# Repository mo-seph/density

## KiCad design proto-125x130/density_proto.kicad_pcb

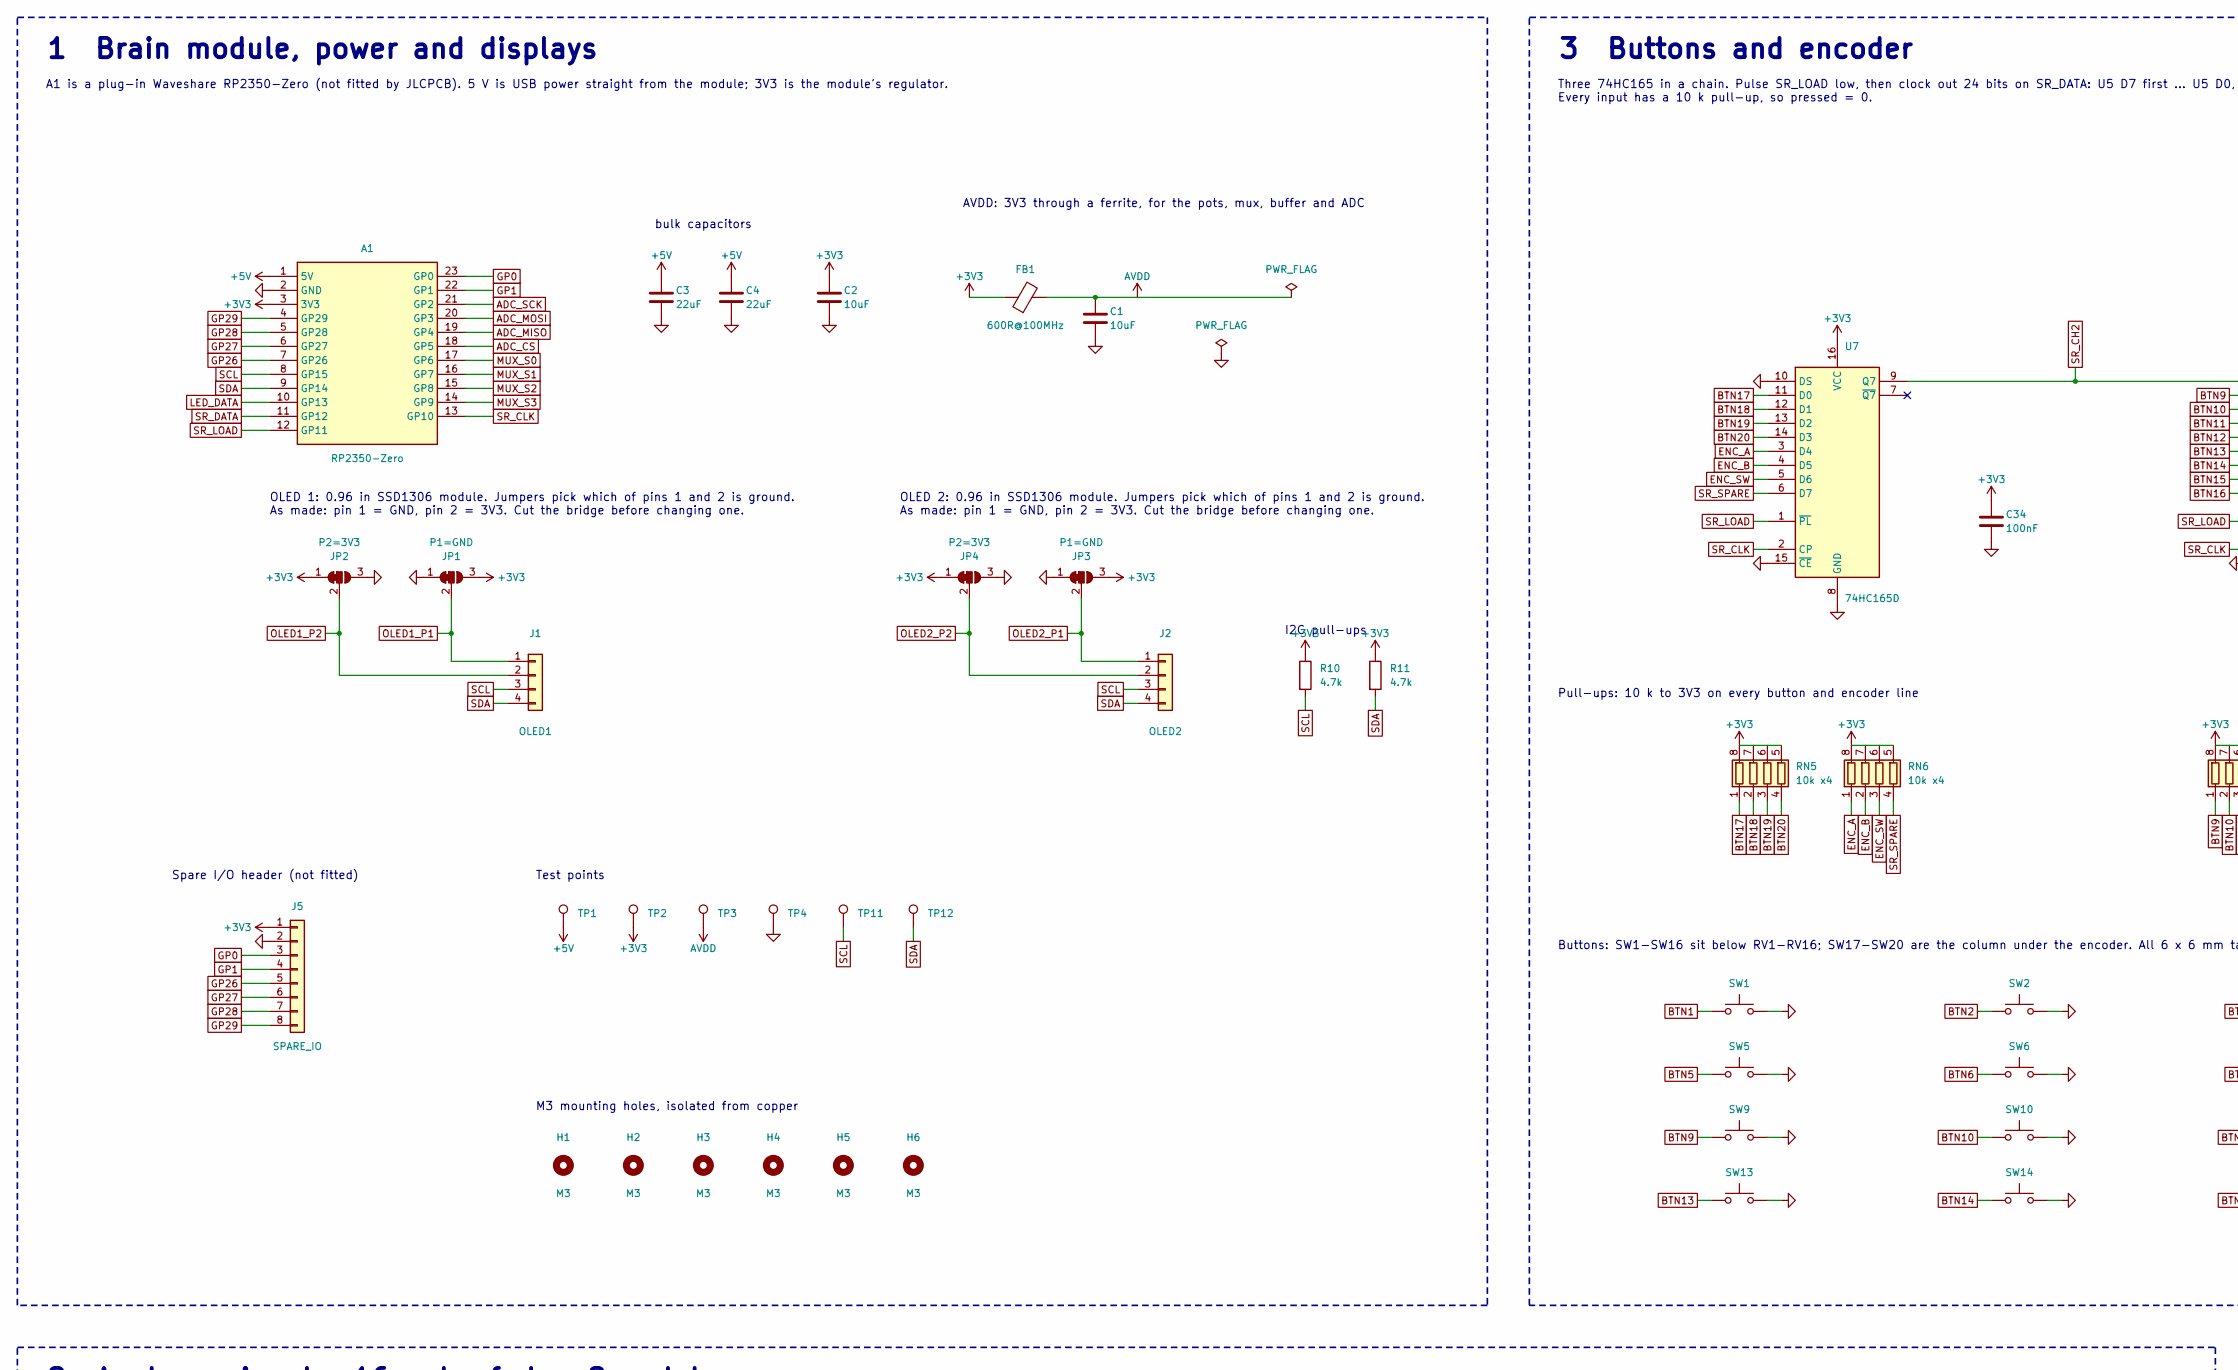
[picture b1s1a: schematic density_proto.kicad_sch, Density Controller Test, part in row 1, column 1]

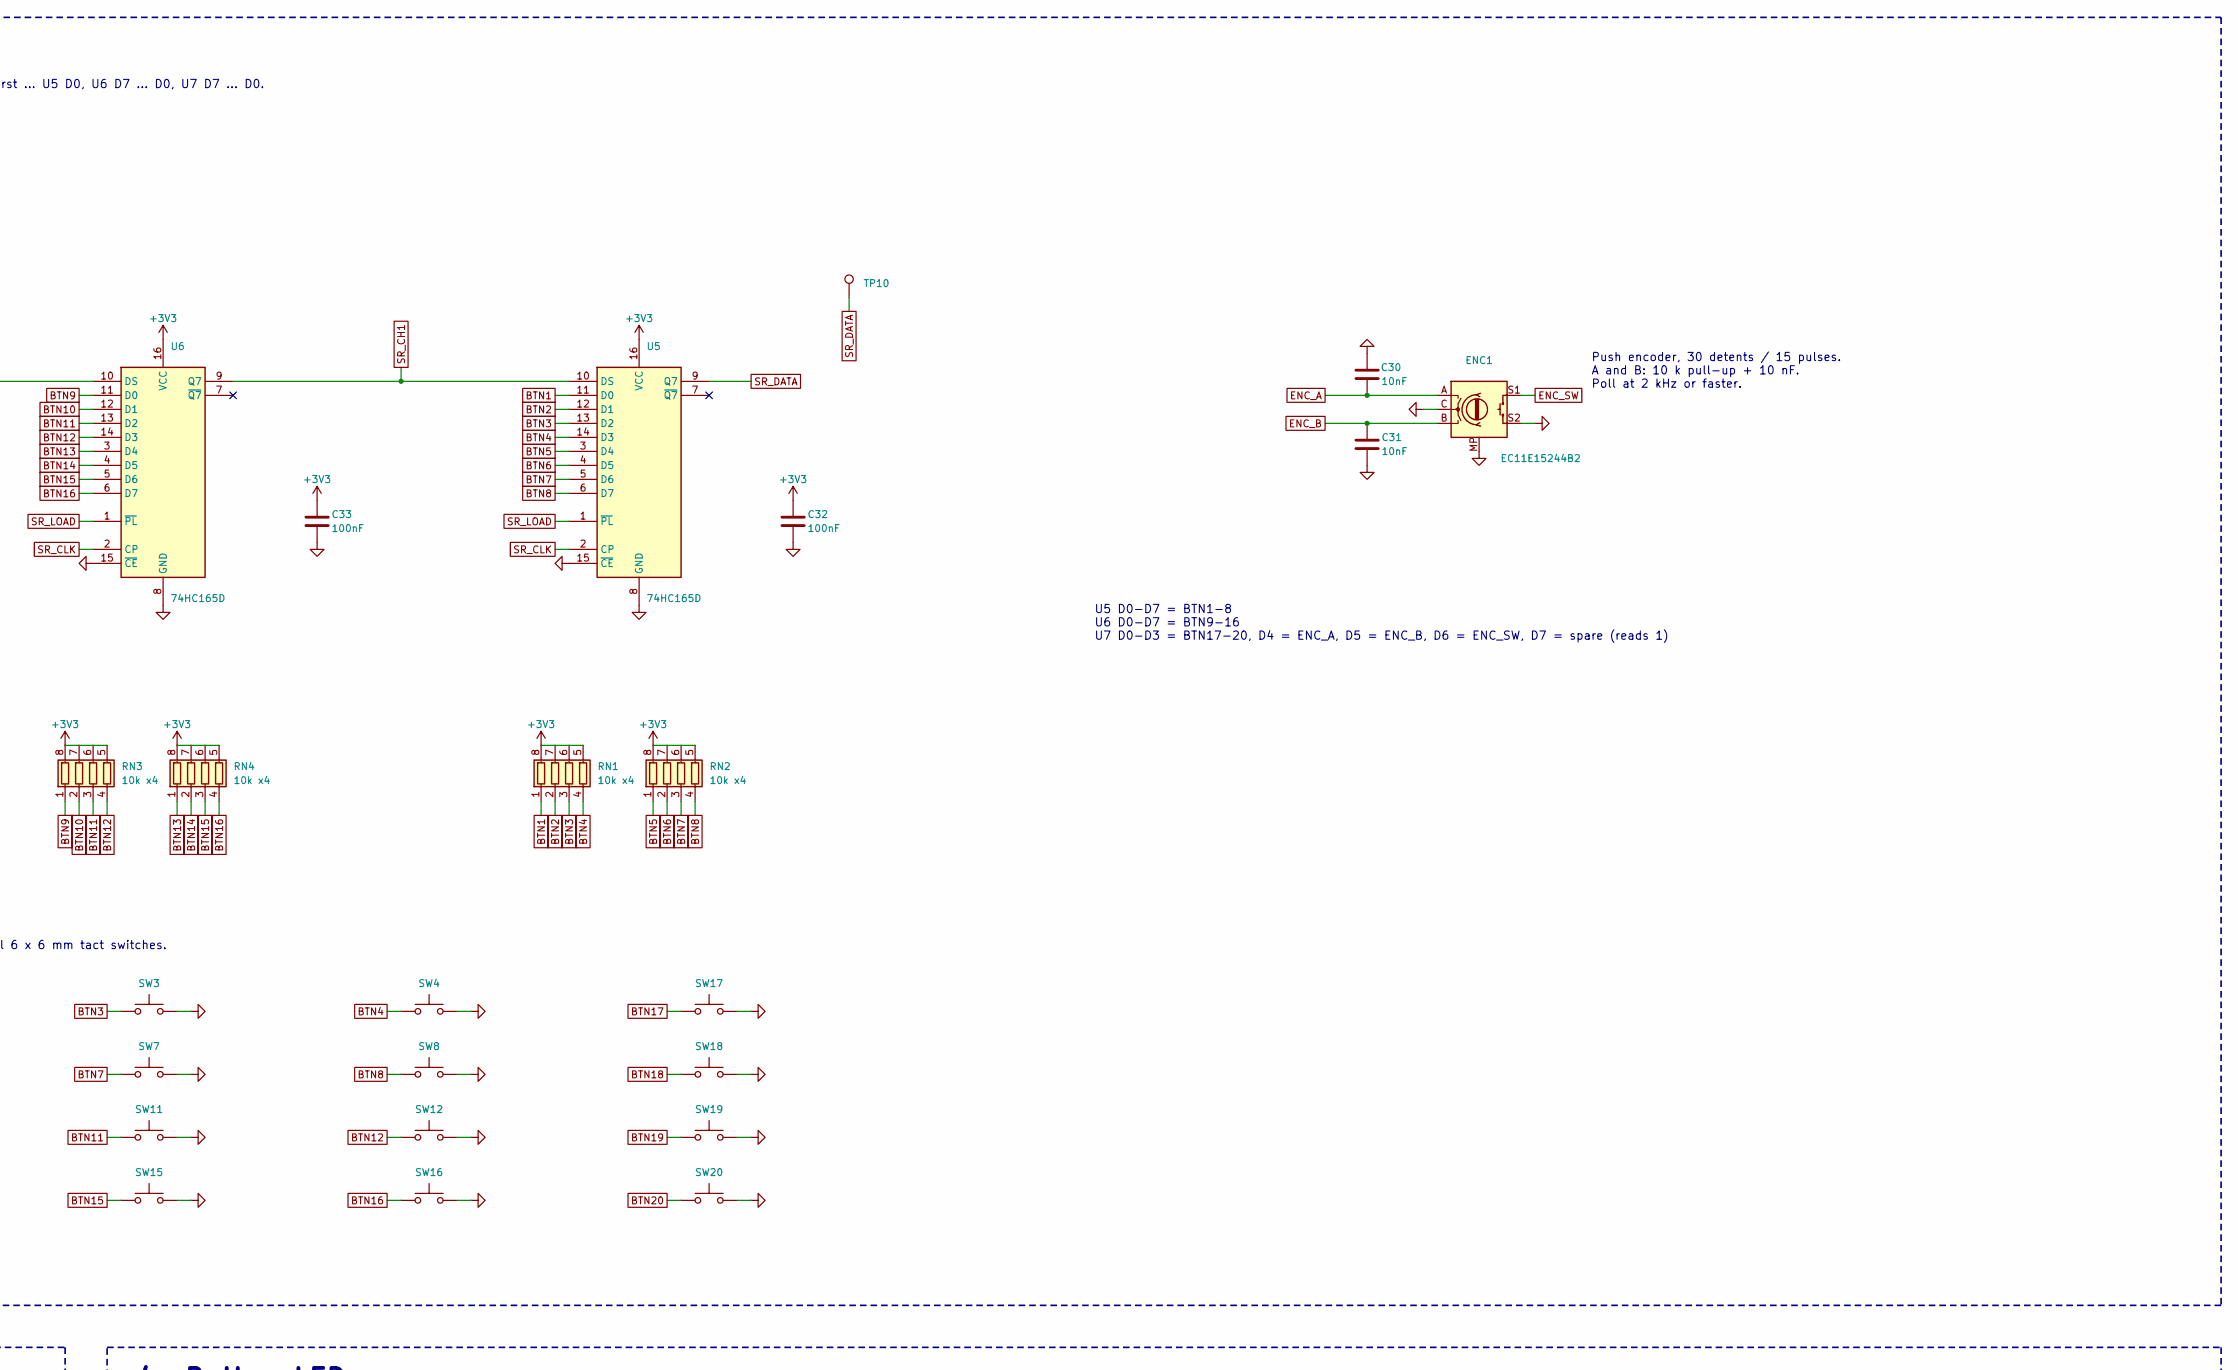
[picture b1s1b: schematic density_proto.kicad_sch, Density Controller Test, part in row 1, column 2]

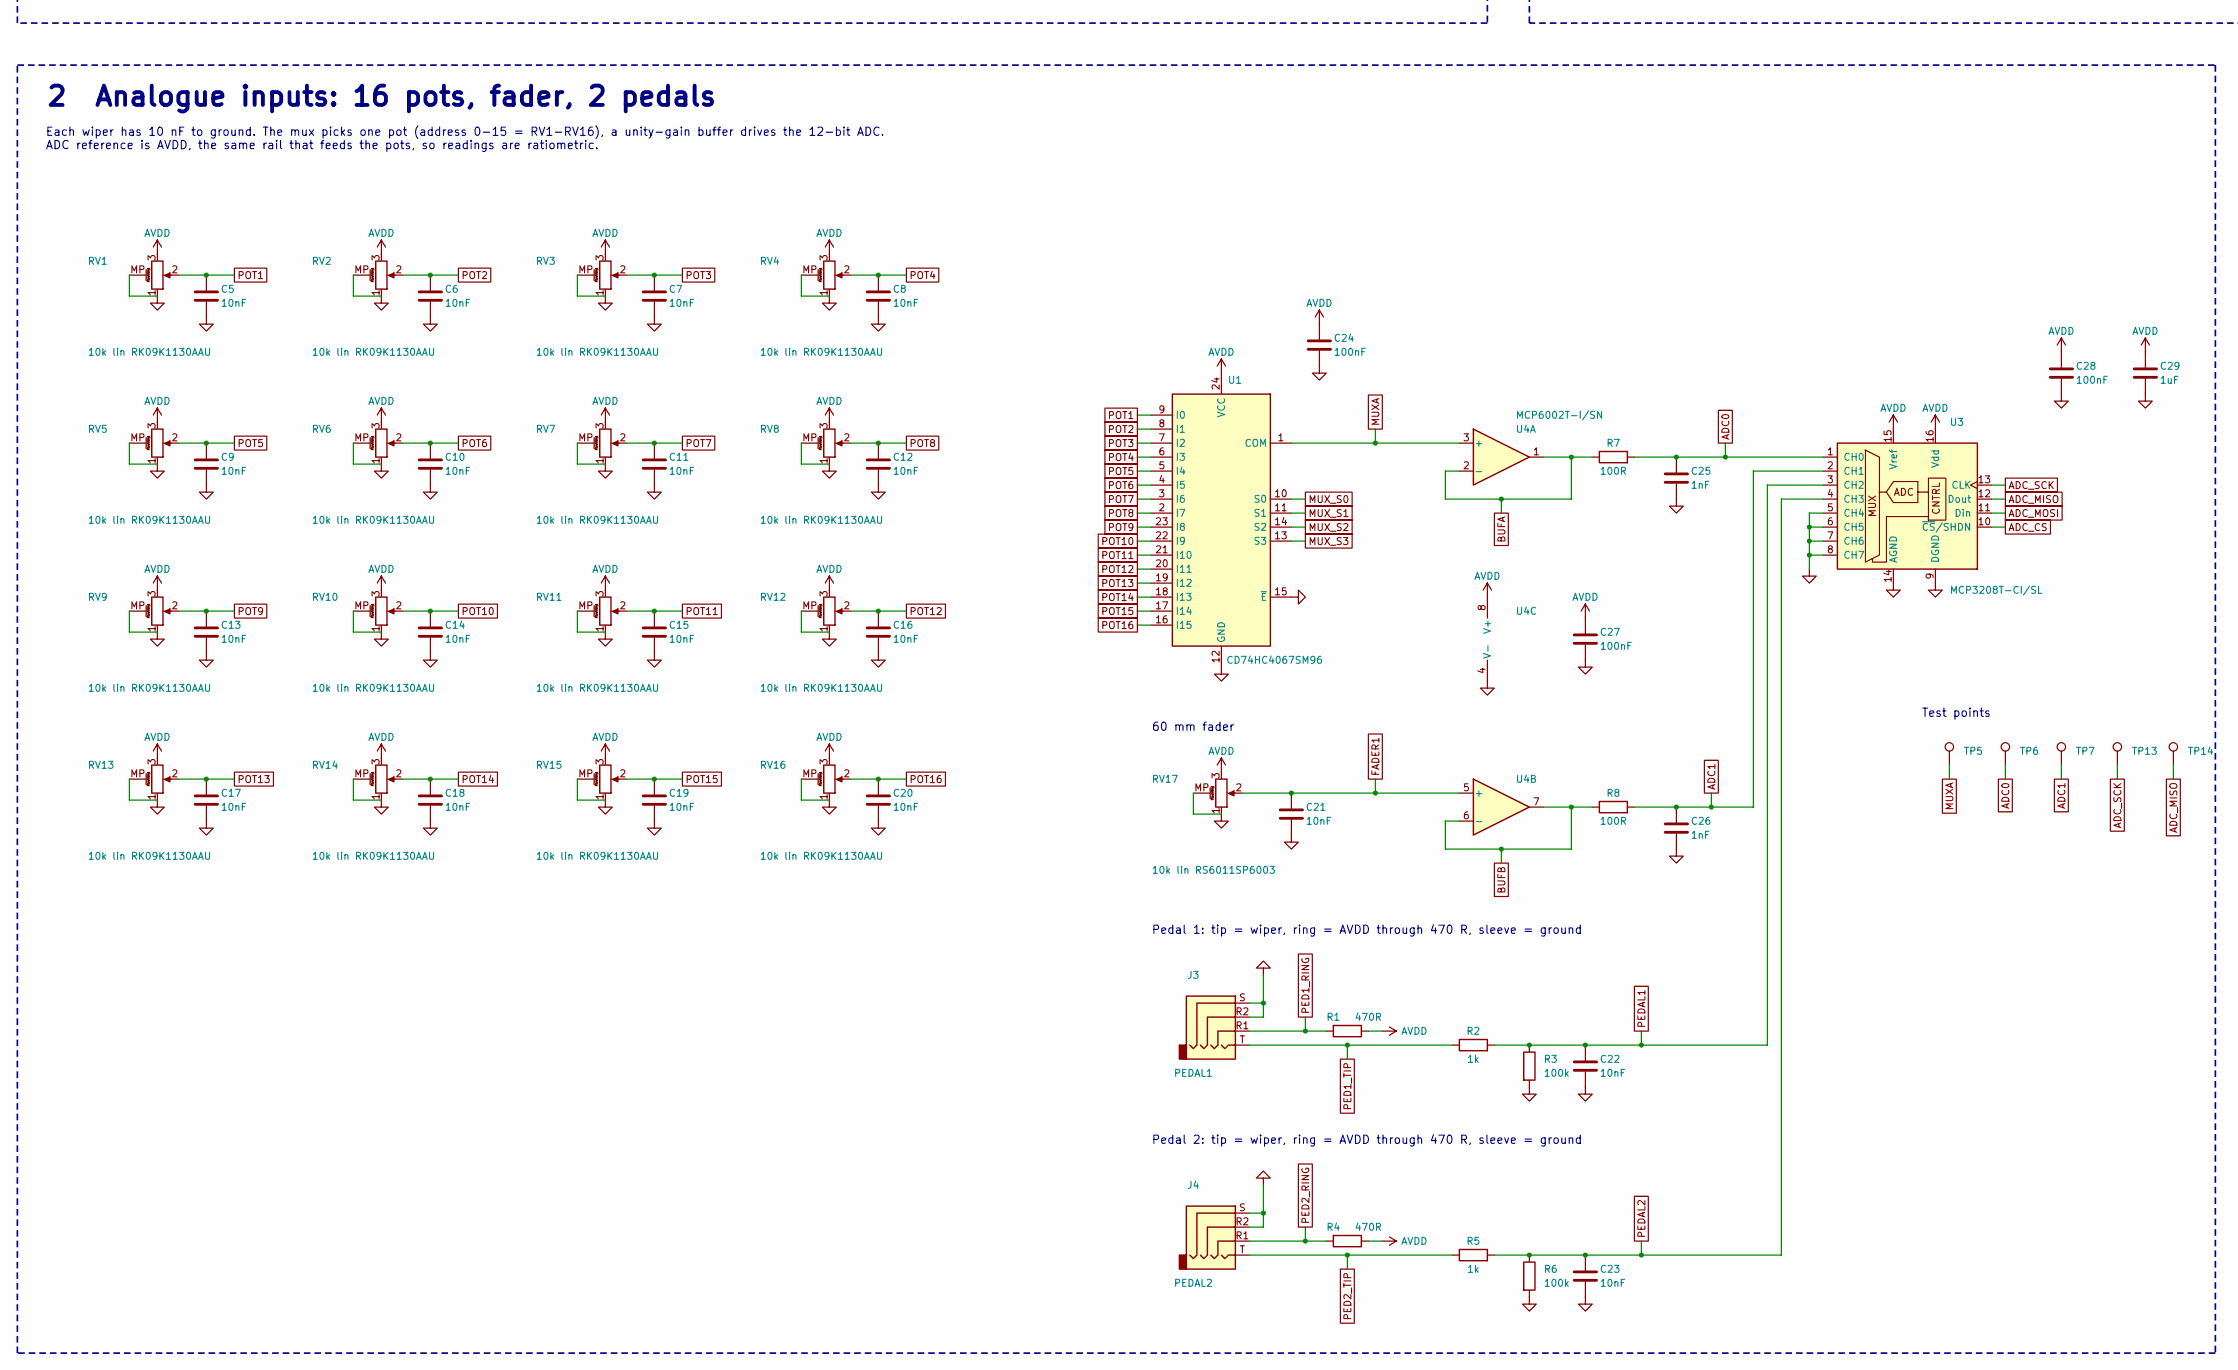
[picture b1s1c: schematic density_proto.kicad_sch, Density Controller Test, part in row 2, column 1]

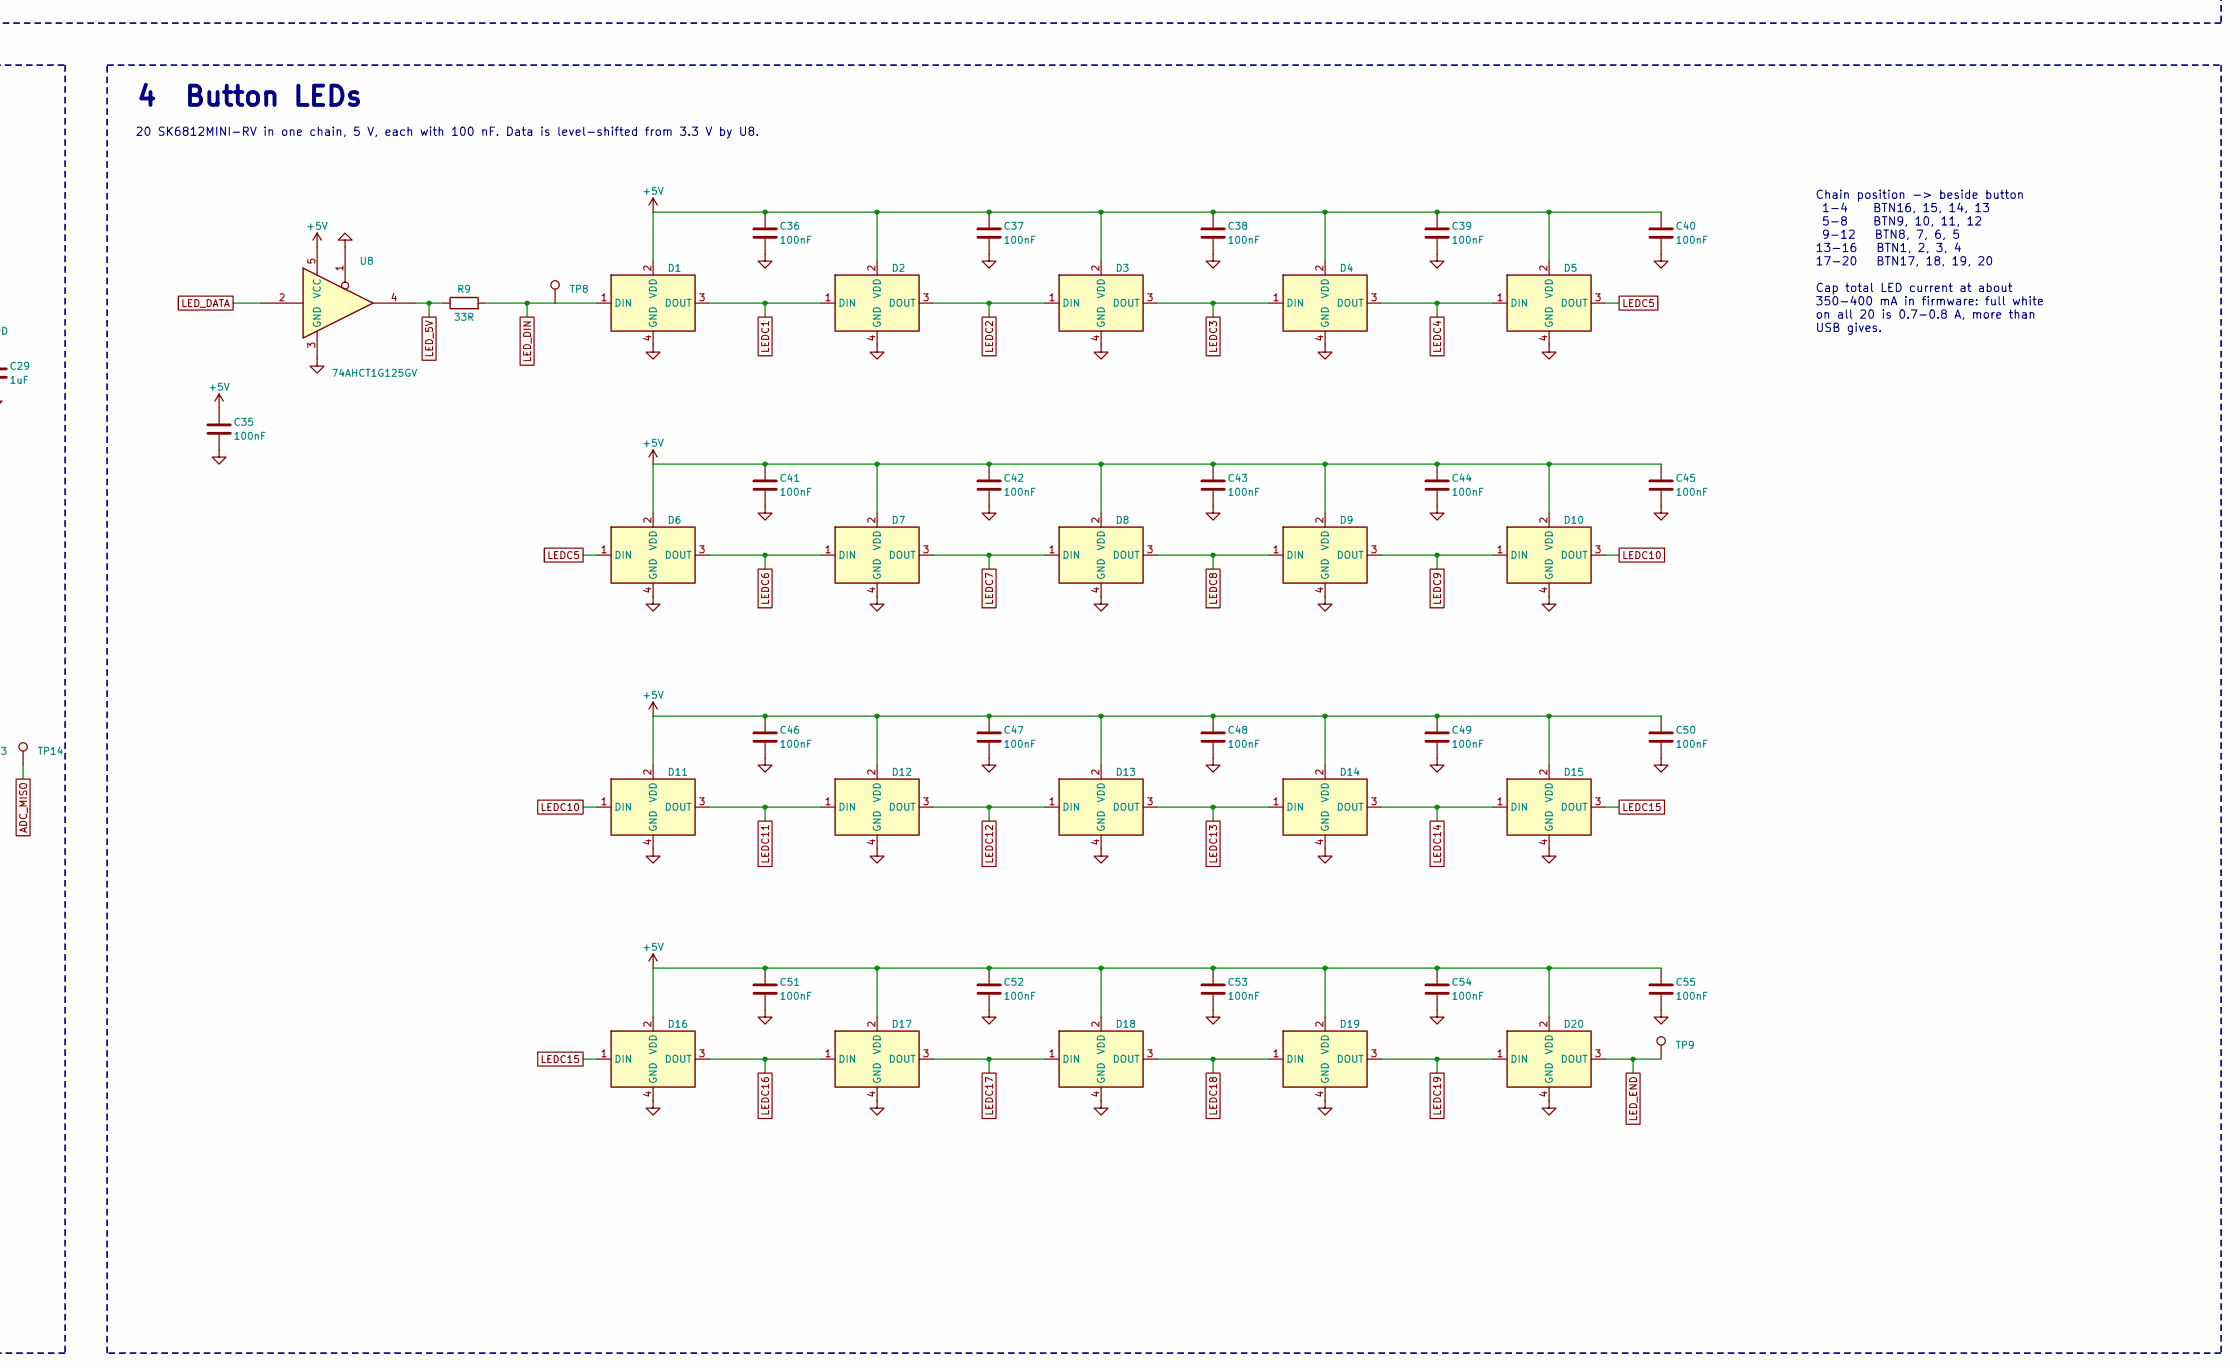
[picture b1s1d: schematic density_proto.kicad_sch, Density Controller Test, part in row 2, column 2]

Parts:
A1: RP2350-Zero; Waveshare_RP2350_Zero_THT
C1, C2: 10uF; C_0805_2012Metric
C3, C4: 22uF; C_0805_2012Metric
C5, C6, C7, C8, C9, C10, C11, C12, C13, C14, C15, C16, C17, C18, C19, C20, C21, C22, C23, C30, C31: 10nF; C_0402_1005Metric
C24, C27, C28, C32, C33, C34, C35, C36, C37, C38, C39, C40, C41, C42, C43, C44, C45, C46, C47, C48, C49, C50, C51, C52, C53, C54, C55: 100nF; C_0402_1005Metric
C25, C26: 1nF; C_0402_1005Metric
C29: 1uF; C_0402_1005Metric
D1, D2, D3, D4, D5, D6, D7, D8, D9, D10, D11, D12, D13, D14, D15, D16, D17, D18, D19, D20: SK6812MINI-RV; LED_SK6812MINI-RV_3.7x3.5mm
ENC1: EC11E15244B2; RotaryEncoder_Alps_EC11E-Switch_Vertical_H20mm
FB1: 600R@100MHz; L_0805_2012Metric
H1, H2, H3, H4, H5, H6: M3; MountingHole_M3_tight
J1: OLED1; OLED_096in_I2C_4Pin
J2: OLED2; OLED_096in_I2C_4Pin
J3: PEDAL1; Jack_3.5mm_PJ320D_Horizontal
J4: PEDAL2; Jack_3.5mm_PJ320D_Horizontal
J5: SPARE_IO; PinHeader_1x08_P2.54mm_Vertical
JP1, JP3: P1=GND; SolderJumper-3_P1.3mm_Bridged12_RoundedPad1.0x1.5mm
JP2, JP4: P2=3V3; SolderJumper-3_P1.3mm_Bridged12_RoundedPad1.0x1.5mm
R1, R4: 470R; R_0402_1005Metric
R2, R5: 1k; R_0402_1005Metric
R3, R6: 100k; R_0402_1005Metric
R7, R8: 100R; R_0402_1005Metric
R9: 33R; R_0402_1005Metric
R10, R11: 4.7k; R_0402_1005Metric
RN1, RN2, RN3, RN4, RN5, RN6: 10k x4; R_Array_Convex_4x0603
RV1, RV2, RV3, RV4, RV5, RV6, RV7, RV8, RV9, RV10, RV11, RV12, RV13, RV14, RV15, RV16: 10k lin RK09K1130AAU; Potentiometer_Alps_RK09K_Single_Vertical
RV17: 10k lin RS6011SP6003; Fader_Alps_RS6011SP_Single
SW1, SW2, SW3, SW4, SW5, SW6, SW7, SW8, SW9, SW10, SW11, SW12, SW13, SW14, SW15, SW16, SW17, SW18, SW19, SW20: 6x6 tact; SW_SPST_PTS645Sx43SMTR92
TP1: 5V; TestPoint_Pad_D1.5mm
TP2: 3V3; TestPoint_Pad_D1.5mm
TP3: AVDD; TestPoint_Pad_D1.5mm
TP4: GND; TestPoint_Pad_D1.5mm
TP5: MUXA; TestPoint_Pad_D1.5mm
TP6: ADC0; TestPoint_Pad_D1.5mm
TP7: ADC1; TestPoint_Pad_D1.5mm
TP8: LED_DIN; TestPoint_Pad_D1.5mm
TP9: LED_END; TestPoint_Pad_D1.5mm
TP10: SR_DATA; TestPoint_Pad_D1.5mm
TP11: SCL; TestPoint_Pad_D1.5mm
TP12: SDA; TestPoint_Pad_D1.5mm
TP13: SCK; TestPoint_Pad_D1.5mm
TP14: MISO; TestPoint_Pad_D1.5mm
U1: CD74HC4067SM96; SSOP-24_5.3x8.2mm_P0.65mm
U3: MCP3208T-CI/SL; SOIC-16_3.9x9.9mm_P1.27mm
U4: MCP6002T-I/SN; SOIC-8_3.9x4.9mm_P1.27mm
U5, U6, U7: 74HC165D; SOIC-16_3.9x9.9mm_P1.27mm
U8: 74AHCT1G125GV; SOT-23-5

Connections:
+3V3: A1.3 (3V3), C2.1, C32.1, C33.1, C34.1, FB1.1, J5.1, JP1.3 (B), JP2.1 (A), JP3.3 (B), JP4.1 (A), R10.1, R11.1, RN1.5 (R4.2), RN1.6 (R3.2), RN1.7 (R2.2), RN1.8 (R1.2), RN2.5 (R4.2), RN2.6 (R3.2), RN2.7 (R2.2), RN2.8 (R1.2), RN3.5 (R4.2), RN3.6 (R3.2), RN3.7 (R2.2), RN3.8 (R1.2), RN4.5 (R4.2), RN4.6 (R3.2), RN4.7 (R2.2), RN4.8 (R1.2), RN5.5 (R4.2), RN5.6 (R3.2), RN5.7 (R2.2), RN5.8 (R1.2), RN6.5 (R4.2), RN6.6 (R3.2), RN6.7 (R2.2), RN6.8 (R1.2), TP2.1, U5.16 (VCC), U6.16 (VCC), U7.16 (VCC)
+5V: A1.1 (5V), C3.1, C4.1, C35.1, C36.1, C37.1, C38.1, C39.1, C40.1, C41.1, C42.1, C43.1, C44.1, C45.1, C46.1, C47.1, C48.1, C49.1, C50.1, C51.1, C52.1, C53.1, C54.1, C55.1, D1.2 (VDD), D2.2 (VDD), D3.2 (VDD), D4.2 (VDD), D5.2 (VDD), D6.2 (VDD), D7.2 (VDD), D8.2 (VDD), D9.2 (VDD), D10.2 (VDD), D11.2 (VDD), D12.2 (VDD), D13.2 (VDD), D14.2 (VDD), D15.2 (VDD), D16.2 (VDD), D17.2 (VDD), D18.2 (VDD), D19.2 (VDD), D20.2 (VDD), TP1.1, U8.5 (VCC)
ADC0: C25.1, R7.2, TP6.1, U3.1 (CH0)
ADC1: C26.1, R8.2, TP7.1, U3.2 (CH1)
ADC_CS: A1.18 (GP5), U3.10 (~CS/SHDN)
ADC_MISO: A1.19 (GP4), TP14.1, U3.12 (Dout)
ADC_MOSI: A1.20 (GP3), U3.11 (Din)
ADC_SCK: A1.21 (GP2), TP13.1, U3.13 (CLK)
AVDD: C1.1, C24.1, C27.1, C28.1, C29.1, FB1.2, R1.1, R4.1, RV1.3, RV2.3, RV3.3, RV4.3, RV5.3, RV6.3, RV7.3, RV8.3, RV9.3, RV10.3, RV11.3, RV12.3, RV13.3, RV14.3, RV15.3, RV16.3, RV17.3, TP3.1, U1.24 (VCC), U3.15 (Vref), U3.16 (Vdd), U4.8 (V+)
BTN1: RN1.1 (R1.1), SW1.1, U5.11 (D0)
BTN2: RN1.2 (R2.1), SW2.1, U5.12 (D1)
BTN3: RN1.3 (R3.1), SW3.1, U5.13 (D2)
BTN4: RN1.4 (R4.1), SW4.1, U5.14 (D3)
BTN5: RN2.1 (R1.1), SW5.1, U5.3 (D4)
BTN6: RN2.2 (R2.1), SW6.1, U5.4 (D5)
BTN7: RN2.3 (R3.1), SW7.1, U5.5 (D6)
BTN8: RN2.4 (R4.1), SW8.1, U5.6 (D7)
BTN9: RN3.1 (R1.1), SW9.1, U6.11 (D0)
BTN10: RN3.2 (R2.1), SW10.1, U6.12 (D1)
BTN11: RN3.3 (R3.1), SW11.1, U6.13 (D2)
BTN12: RN3.4 (R4.1), SW12.1, U6.14 (D3)
BTN13: RN4.1 (R1.1), SW13.1, U6.3 (D4)
BTN14: RN4.2 (R2.1), SW14.1, U6.4 (D5)
BTN15: RN4.3 (R3.1), SW15.1, U6.5 (D6)
BTN16: RN4.4 (R4.1), SW16.1, U6.6 (D7)
BTN17: RN5.1 (R1.1), SW17.1, U7.11 (D0)
BTN18: RN5.2 (R2.1), SW18.1, U7.12 (D1)
BTN19: RN5.3 (R3.1), SW19.1, U7.13 (D2)
BTN20: RN5.4 (R4.1), SW20.1, U7.14 (D3)
BUFA: R7.1, U4.1, U4.2 (-)
BUFB: R8.1, U4.6 (-), U4.7
ENC_A: C30.1, ENC1.A, RN6.1 (R1.1), U7.3 (D4)
ENC_B: C31.1, ENC1.B, RN6.2 (R2.1), U7.4 (D5)
ENC_SW: ENC1.S1, RN6.3 (R3.1), U7.5 (D6)
FADER1: C21.1, RV17.2, U4.5 (+)
GND: A1.2 (GND), C1.2, C2.2, C3.2, C4.2, C5.2, C6.2, C7.2, C8.2, C9.2, C10.2, C11.2, C12.2, C13.2, C14.2, C15.2, C16.2, C17.2, C18.2, C19.2, C20.2, C21.2, C22.2, C23.2, C24.2, C25.2, C26.2, C27.2, C28.2, C29.2, C30.2, C31.2, C32.2, C33.2, C34.2, C35.2, C36.2, C37.2, C38.2, C39.2, C40.2, C41.2, C42.2, C43.2, C44.2, C45.2, C46.2, C47.2, C48.2, C49.2, C50.2, C51.2, C52.2, C53.2, C54.2, C55.2, D1.4 (GND), D2.4 (GND), D3.4 (GND), D4.4 (GND), D5.4 (GND), D6.4 (GND), D7.4 (GND), D8.4 (GND), D9.4 (GND), D10.4 (GND), D11.4 (GND), D12.4 (GND), D13.4 (GND), D14.4 (GND), D15.4 (GND), D16.4 (GND), D17.4 (GND), D18.4 (GND), D19.4 (GND), D20.4 (GND), ENC1.C, ENC1.MP, ENC1.S2, J3.R2, J3.S, J4.R2, J4.S, J5.2, JP1.1 (A), JP2.3 (B), JP3.1 (A), JP4.3 (B), R3.2, R6.2, RV1.1, RV1.MP (MountPin), RV2.1, RV2.MP (MountPin), RV3.1, RV3.MP (MountPin), RV4.1, RV4.MP (MountPin), RV5.1, RV5.MP (MountPin), RV6.1, RV6.MP (MountPin), RV7.1, RV7.MP (MountPin), RV8.1, RV8.MP (MountPin), RV9.1, RV9.MP (MountPin), RV10.1, RV10.MP (MountPin), RV11.1, RV11.MP (MountPin), RV12.1, RV12.MP (MountPin), RV13.1, RV13.MP (MountPin), RV14.1, RV14.MP (MountPin), RV15.1, RV15.MP (MountPin), RV16.1, RV16.MP (MountPin), RV17.1, RV17.MP (MountPin), SW1.2, SW2.2, SW3.2, SW4.2, SW5.2, SW6.2, SW7.2, SW8.2, SW9.2, SW10.2, SW11.2, SW12.2, SW13.2, SW14.2, SW15.2, SW16.2, SW17.2, SW18.2, SW19.2, SW20.2, TP4.1, U1.12 (GND), U1.15 (~E), U3.5 (CH4), U3.6 (CH5), U3.7 (CH6), U3.8 (CH7), U3.9 (DGND), U3.14 (AGND), U4.4 (V-), U5.8 (GND), U5.15 (~CE), U6.8 (GND), U6.15 (~CE), U7.8 (GND), U7.10 (DS), U7.15 (~CE), U8.1, U8.3 (GND)
GP0: A1.23 (GP0), J5.3
GP1: A1.22 (GP1), J5.4
GP26: A1.7 (GP26), J5.5
GP27: A1.6 (GP27), J5.6
GP28: A1.5 (GP28), J5.7
GP29: A1.4 (GP29), J5.8
LEDC1: D1.3 (DOUT), D2.1 (DIN)
LEDC2: D2.3 (DOUT), D3.1 (DIN)
LEDC3: D3.3 (DOUT), D4.1 (DIN)
LEDC4: D4.3 (DOUT), D5.1 (DIN)
LEDC5: D5.3 (DOUT), D6.1 (DIN)
LEDC6: D6.3 (DOUT), D7.1 (DIN)
LEDC7: D7.3 (DOUT), D8.1 (DIN)
LEDC8: D8.3 (DOUT), D9.1 (DIN)
LEDC9: D9.3 (DOUT), D10.1 (DIN)
LEDC10: D10.3 (DOUT), D11.1 (DIN)
LEDC11: D11.3 (DOUT), D12.1 (DIN)
LEDC12: D12.3 (DOUT), D13.1 (DIN)
LEDC13: D13.3 (DOUT), D14.1 (DIN)
LEDC14: D14.3 (DOUT), D15.1 (DIN)
LEDC15: D15.3 (DOUT), D16.1 (DIN)
LEDC16: D16.3 (DOUT), D17.1 (DIN)
LEDC17: D17.3 (DOUT), D18.1 (DIN)
LEDC18: D18.3 (DOUT), D19.1 (DIN)
LEDC19: D19.3 (DOUT), D20.1 (DIN)
LED_5V: R9.1, U8.4
LED_DATA: A1.10 (GP13), U8.2
LED_DIN: D1.1 (DIN), R9.2, TP8.1
LED_END: D20.3 (DOUT), TP9.1
MUXA: TP5.1, U1.1 (COM), U4.3 (+)
MUX_S0: A1.17 (GP6), U1.10 (S0)
MUX_S1: A1.16 (GP7), U1.11 (S1)
MUX_S2: A1.15 (GP8), U1.14 (S2)
MUX_S3: A1.14 (GP9), U1.13 (S3)
OLED1_P1: J1.1, JP1.2 (C)
OLED1_P2: J1.2, JP2.2 (C)
OLED2_P1: J2.1, JP3.2 (C)
OLED2_P2: J2.2, JP4.2 (C)
PED1_RING: J3.R1, R1.2
PED1_TIP: J3.T, R2.1
PED2_RING: J4.R1, R4.2
PED2_TIP: J4.T, R5.1
PEDAL1: C22.1, R2.2, R3.1, U3.3 (CH2)
PEDAL2: C23.1, R5.2, R6.1, U3.4 (CH3)
POT1: C5.1, RV1.2, U1.9 (I0)
POT2: C6.1, RV2.2, U1.8 (I1)
POT3: C7.1, RV3.2, U1.7 (I2)
POT4: C8.1, RV4.2, U1.6 (I3)
POT5: C9.1, RV5.2, U1.5 (I4)
POT6: C10.1, RV6.2, U1.4 (I5)
POT7: C11.1, RV7.2, U1.3 (I6)
POT8: C12.1, RV8.2, U1.2 (I7)
POT9: C13.1, RV9.2, U1.23 (I8)
POT10: C14.1, RV10.2, U1.22 (I9)
POT11: C15.1, RV11.2, U1.21 (I10)
POT12: C16.1, RV12.2, U1.20 (I11)
POT13: C17.1, RV13.2, U1.19 (I12)
POT14: C18.1, RV14.2, U1.18 (I13)
POT15: C19.1, RV15.2, U1.17 (I14)
POT16: C20.1, RV16.2, U1.16 (I15)
SCL: A1.8 (GP15), J1.3, J2.3, R10.2, TP11.1
SDA: A1.9 (GP14), J1.4, J2.4, R11.2, TP12.1
SR_CH1: U5.10 (DS), U6.9 (Q7)
SR_CH2: U6.10 (DS), U7.9 (Q7)
SR_CLK: A1.13 (GP10), U5.2 (CP), U6.2 (CP), U7.2 (CP)
SR_DATA: A1.11 (GP12), TP10.1, U5.9 (Q7)
SR_LOAD: A1.12 (GP11), U5.1 (~PL), U6.1 (~PL), U7.1 (~PL)
SR_SPARE: RN6.4 (R4.1), U7.6 (D7)

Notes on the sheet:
1 Brain module, power and displays
A1 is a plug-in Waveshare RP2350-Zero (not fitted by JLCPCB). 5 V is USB power straight from the module; 3V3 is the module's regulator.
bulk capacitors
AVDD: 3V3 through a ferrite, for the pots, mux, buffer and ADC
OLED 1: 0.96 in SSD1306 module. Jumpers pick which of pins 1 and 2 is ground. As made: pin 1 = GND, pin 2 = 3V3. Cut the bridge before changing one.
OLED 2: 0.96 in SSD1306 module. Jumpers pick which of pins 1 and 2 is ground. As made: pin 1 = GND, pin 2 = 3V3. Cut the bridge before changing one.
I2C pull-ups
Spare I/O header (not fitted)
Test points
M3 mounting holes, isolated from copper
2 Analogue inputs: 16 pots, fader, 2 pedals
Each wiper has 10 nF to ground. The mux picks one pot (address 0-15 = RV1-RV16), a unity-gain buffer drives the 12-bit ADC. ADC reference is AVDD, the same rail that feeds the pots, so readings are ratiometric.
60 mm fader
Pedal 1: tip = wiper, ring = AVDD through 470 R, sleeve = ground
Pedal 2: tip = wiper, ring = AVDD through 470 R, sleeve = ground
3 Buttons and encoder
Three 74HC165 in a chain. Pulse SR_LOAD low, then clock out 24 bits on SR_DATA: U5 D7 first ... U5 D0, U6 D7 ... D0, U7 D7 ... D0. Every input has a 10 k pull-up, so pressed = 0.
Push encoder, 30 detents / 15 pulses. A and B: 10 k pull-up + 10 nF. Poll at 2 kHz or faster.
Pull-ups: 10 k to 3V3 on every button and encoder line
Buttons: SW1-SW16 sit below RV1-RV16; SW17-SW20 are the column under the encoder. All 6 x 6 mm tact switches.
U5 D0-D7 = BTN1-8 U6 D0-D7 = BTN9-16 U7 D0-D3 = BTN17-20, D4 = ENC_A, D5 = ENC_B, D6 = ENC_SW, D7 = spare (reads 1)
4 Button LEDs
20 SK6812MINI-RV in one chain, 5 V, each with 100 nF. Data is level-shifted from 3.3 V by U8.
Chain position -> beside button 1-4 BTN16, 15, 14, 13 5-8 BTN9, 10, 11, 12 9-12 BTN8, 7, 6, 5 13-16 BTN1, 2, 3, 4 17-20 BTN17, 18, 19, 20 Cap total LED current at about 350-400 mA in firmware: full white on all 20 is 0.7-0.8 A, more than USB gives.

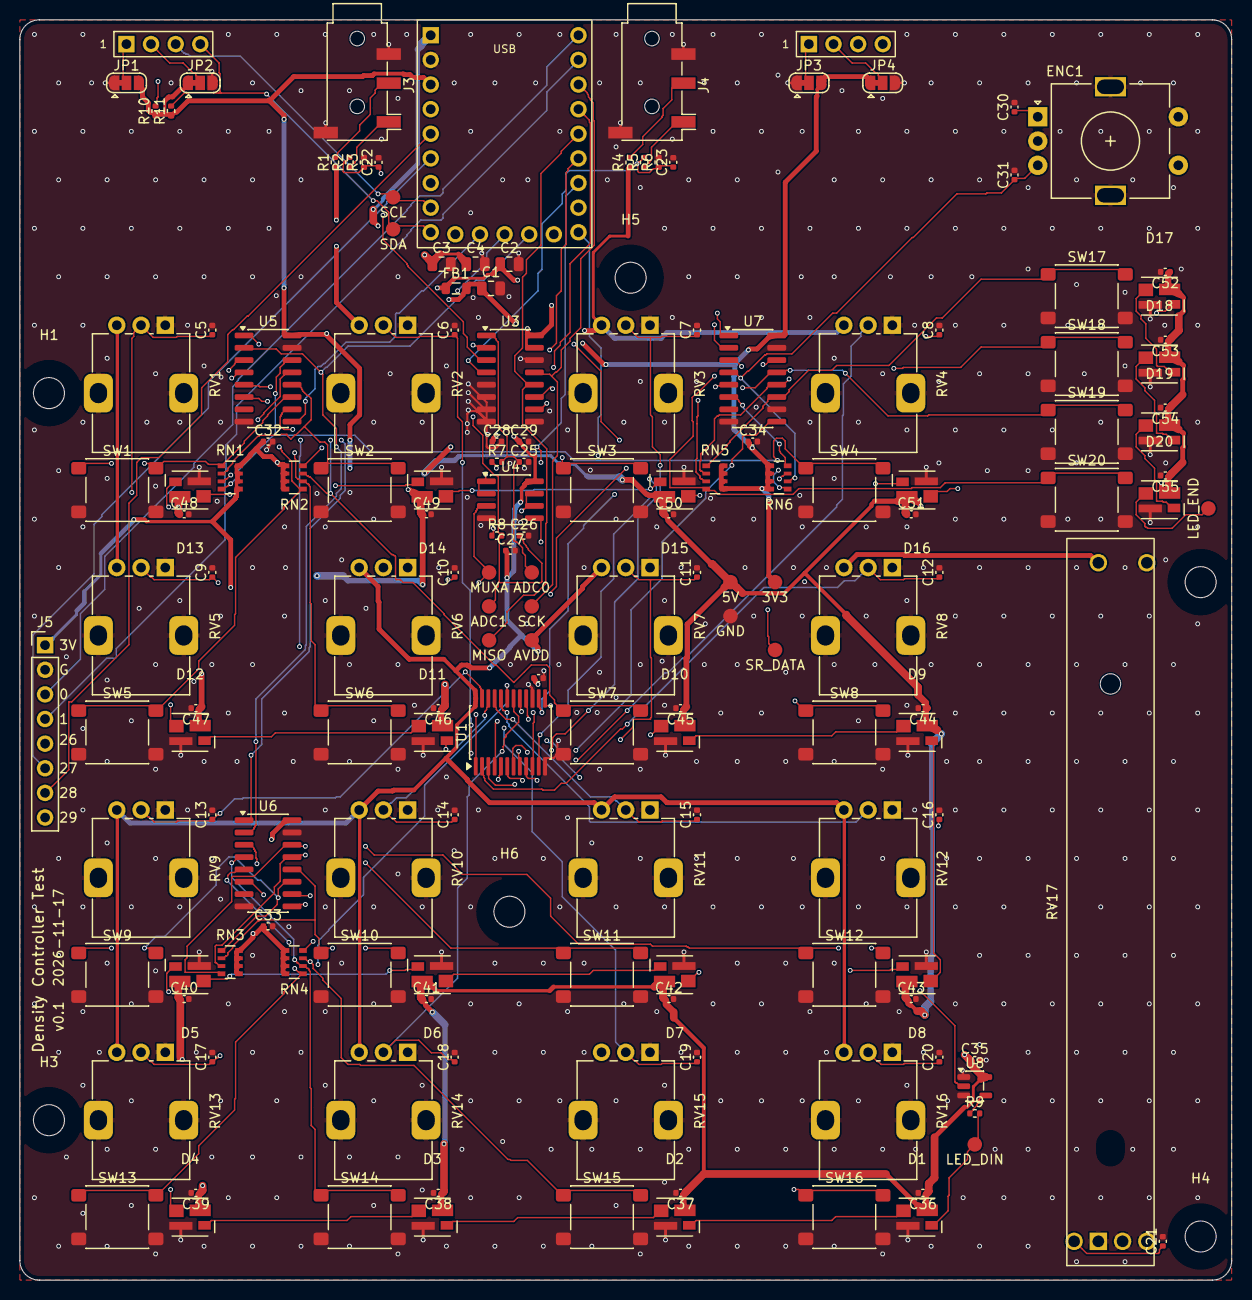
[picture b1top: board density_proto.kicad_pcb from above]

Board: 4 copper layers, 125.0 x 130.0 mm, 168 parts (0 on the bottom side), 104 nets.

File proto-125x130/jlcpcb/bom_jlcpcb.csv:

Comment,Designator,Footprint,LCSC Part #
600R@100MHz,FB1,L_0805_2012Metric,C1017
10uF,"C1,C2",C_0805_2012Metric,C15850
22uF,"C3,C4",C_0805_2012Metric,C45783
10k lin RK09K1130AAU,"RV1,RV2,RV3,RV4,RV5,RV6,RV7,RV8,RV9,RV10,RV11,RV12,RV13,RV14,RV15,RV16",Potentiometer_Alps_RK09K_Single_Vertical,C202373
10nF,"C5,C6,C7,C8,C9,C10,C11,C12,C13,C14,C15,C16,C17,C18,C19,C20,C21,C22,C23,C30,C31",C_0402_1005Metric,C15195
10k lin RS6011SP6003,RV17,Fader_Alps_RS6011SP_Single,C370993
PJ-320D,"J3,J4",Jack_3.5mm_PJ320D_Horizontal,C19189088
470R,"R1,R4",R_0402_1005Metric,C25117
1k,"R2,R5",R_0402_1005Metric,C11702
100k,"R3,R6",R_0402_1005Metric,C25741
CD74HC4067SM96,U1,SSOP-24_5.3x8.2mm_P0.65mm,C98457
100nF,"C24,C27,C28,C32,C33,C34,C35,C36,C37,C38,C39,C40,C41,C42,C43,C44,C45,C46,C47,C48,C49,C50,C51,C52,C53,C54,C55",C_0402_1005Metric,C1525
100R,"R7,R8",R_0402_1005Metric,C25076
1nF,"C25,C26",C_0402_1005Metric,C1523
MCP3208T-CI/SL,U3,SOIC-16_3.9x9.9mm_P1.27mm,C626764
1uF,C29,C_0402_1005Metric,C52923
6x6 tact,"SW1,SW2,SW3,SW4,SW5,SW6,SW7,SW8,SW9,SW10,SW11,SW12,SW13,SW14,SW15,SW16,SW17,SW18,SW19,SW20",SW_SPST_PTS645Sx43SMTR92,C127509
EC11E15244B2,ENC1,RotaryEncoder_Alps_EC11E-Switch_Vertical_H20mm,C470754
74HC165D,"U5,U6,U7",SOIC-16_3.9x9.9mm_P1.27mm,C5613
10k x4,"RN1,RN2,RN3,RN4,RN5,RN6",R_Array_Convex_4x0603,C29718
74AHCT1G125GV,U8,SOT-23-5,C52140417
33R,R9,R_0402_1005Metric,C25105
SK6812MINI-RV,"D1,D2,D3,D4,D5,D6,D7,D8,D9,D10,D11,D12,D13,D14,D15,D16,D17,D18,D19,D20",LED_SK6812MINI-RV_3.7x3.5mm,C7279958
4.7k,"R10,R11",R_0402_1005Metric,C25900
MCP6002T-I/SN,U4,SOIC-8_3.9x4.9mm_P1.27mm,C7377
